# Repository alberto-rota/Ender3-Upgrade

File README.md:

# Ender3-Upgrade
A collection of upgrades and mods I installed on my Creality Ender 3.

This repository includes:
- A CAD model of the 3D printer, that includes the modifications made to the original design
- Downloadable `stl` files for the 3D printed parts
- The Marlin 2.0 firmware installed
- The PCB design for the custom electronic boards
  
***

<p align="center"> 
<a href="https://minhaskamal.github.io/DownGit/#/home?url=https://github.com/alberto-rota/Ender3-Upgrade/Printables">
<picture>
  <source media="(prefers-color-scheme: dark)" srcset="readme/download_stls_light.png">
   
</picture>
</a> </p>
All parts have been printed in standard 1.75 PLA filament, with a 4mm nozzle. They can be printer on any 3D printer, from hobbyist to professional. Print settings change depending on the part and the printer, but as long as a good bed adhesion is achieved, all parts will come out fine. The only part that requires a bit of support material in some place is the "Back case".

***
## Overview
The full Ender3 printer complete with all the upgrades is depicted below:

***
### Print Server
A Raspberry Pi 3A+ is used to host an OctoPrint server to remotely control and monitor the 3D printer. The Pi is powered from its separate power supply, connected to the printer via a USB cable, connected to the local network via WiFi (this was a limitation due to the available 3A+ model, a different model will be connected via Ethernet) and to an external USB webcam via a USB cable. A OTG USB hub (not in the picture) is necessary if using a 3A+

**NOTE:** This project was carried out during the COVID-19 pandemic, with the limited availability of electronics component (Pis cost more than 200€).

In order to control "high-power" components from Octoprint (USB lights, custom Noctua Fans), a custom PCB mounting a set of MOSFET switches was custom designed and integrated in the printer. The PCB mounts 2 Buck converters to step down the 24V of the Power supply to 5V (for the USB lights) and 12V (for the Noctua fans) and is connected to the Raspberry via the GPIO pins.

The render and the schematics of the PCS are shown below:

The Pi, PCB, hub and cables are all positioned into a custom 3D printed case, that is mounted in the V-slots of the aluminum extruded profiles.

***
### USB light bar

A USB LED strip is mounted on the top horizontal frame of the printer, to provide a light source for the print bed. Two supports were necessary in order to hold the magnets that came with the LED bar and that hold it in place. The supports and custom clips that hold the cable in place are custom and designed for the V-slots.
The lights are controlled via Octoprint through the GPIO plugin.

***
### Drawers
A set of 2 easy-access drawers have been positioned between the screen and the Y-Axis frame. The drawer container is, again, designed to fit in the V-slots of the aluminum extrusion.

Moreover, a set of 4 drawers has been placed behind the LCD screen of the printer. These drawers hold items which are more rarely accessed: nozzles, screws, springs, *etc.* The drwer container is held in place by the same screws that hold the LCD screen.

***
### Cable chain
A better cable management job was ensured with a set of cable covers that form a chain holding the cables tidy. One of this chain holds the cables that connect to the heated bed, the other holds the cables that connect to the extruder. The chain is mounted on the back of the printer, on the aluminum extrusion.

***
### Webcam Mount
A 3D printed mounting piece for a webcam. The shape and hole position are specific for the USB webcam I had at hand. The mount is designed to slide into the V-slots of the aluminum extruded profiles, with enough play to easily adjust its position along the extrusion.

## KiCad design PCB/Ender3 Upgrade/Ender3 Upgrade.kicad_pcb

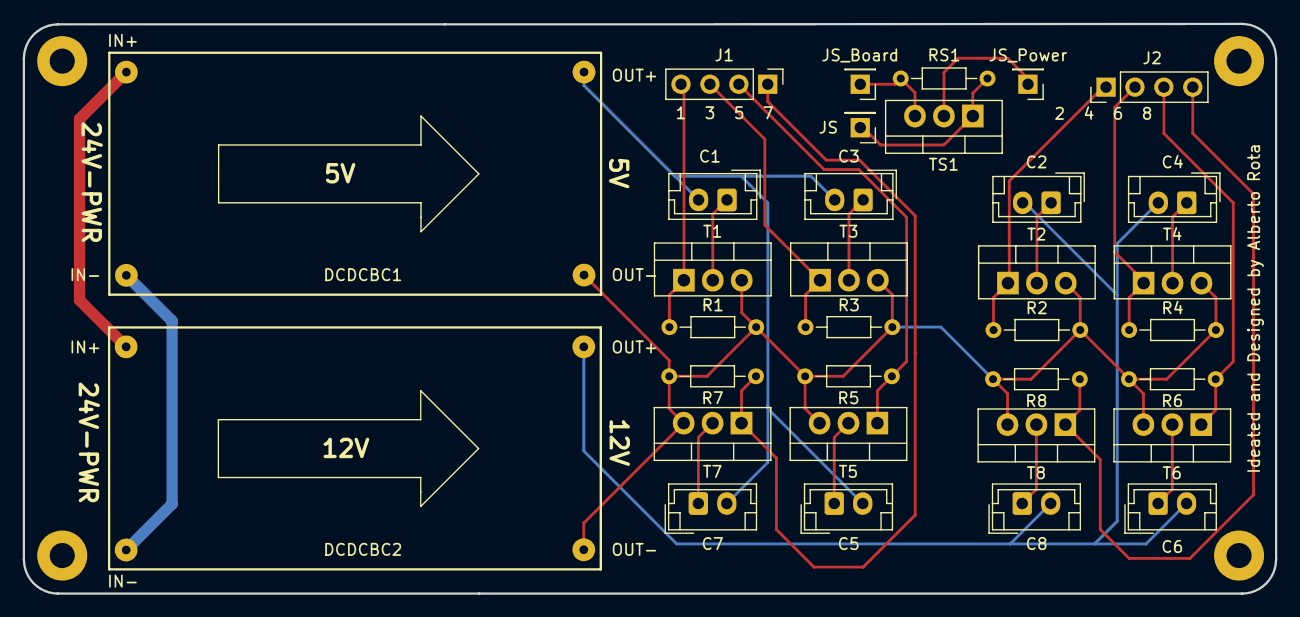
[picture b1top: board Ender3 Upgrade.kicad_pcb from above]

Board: 2 copper layers, 110.0 x 50.0 mm, 33 parts (0 on the bottom side), 24 nets.

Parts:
C1, C2, C3, C4, C5, C6, C7, C8: Conn_01x02; JST_EH_B2B-EH-A_1x02_P2.50mm_Vertical
DCDCBC1: DCDC 24-5; BuckConverter
DCDCBC2: DCDC 24-12; BuckConverter
J1, J2: Conn_01x04_Male; PinHeader_1x04_P2.54mm_Vertical
JS: Conn_01x01_Male; PinHeader_1x01_P2.54mm_Vertical
JS_Board: Conn_01x01_Male; PinHeader_1x01_P2.54mm_Vertical
JS_Power: Conn_01x01_Male; PinHeader_1x01_P2.54mm_Vertical
R1, R2, R3, R4, R5, R6, R7, R8: R1; R_Axial_DIN0204_L3.6mm_D1.6mm_P7.62mm_Horizontal
RS1: R1; R_Axial_DIN0204_L3.6mm_D1.6mm_P7.62mm_Horizontal
T1, T2, T3, T4, T5, T6, T7, T8: IRLZ34N; TO-220-3_Vertical
TS1: IRLZ34N; TO-220-3_Vertical

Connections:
5V: C1.2, C3.2, C5.2, C7.2, DCDCBC1.4
12V: C2.2, C4.2, C6.2, C8.2, DCDCBC2.4
+24V: DCDCBC1.2, DCDCBC2.2
GND: DCDCBC1.3, DCDCBC2.3, R1.2, R2.2, R3.2, R4.2, R5.2, R6.2, R7.2, R8.2, T1.3, T2.3, T3.3, T4.3, T5.3, T6.3, T7.3, T8.3
GNDPWR: DCDCBC1.1, DCDCBC2.1
unnamed: C1.1, T1.2
unnamed: C2.1, T2.2
unnamed: C3.1, T3.2
unnamed: C4.1, T4.2
unnamed: C5.1, T5.2
unnamed: C6.1, T6.2
unnamed: C7.1, T7.2
unnamed: C8.1, T8.2
unnamed: J1.1, R7.1, T7.1
unnamed: J1.2, R5.1, T5.1
unnamed: J1.3, R3.1, T3.1
unnamed: J1.4, R1.1, T1.1
unnamed: J2.1, R2.1, T2.1
unnamed: J2.2, R4.1, T4.1
unnamed: J2.3, R6.1, T6.1
unnamed: J2.4, R8.1, T8.1
unnamed: JS_Board.1, RS1.2, TS1.3
unnamed: JS.1, RS1.1, TS1.1
unnamed: JS_Power.1, TS1.2

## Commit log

2023-01-05 Firmware
2023-01-05 Initial update
2023-01-06 LED Wire Clip
2023-01-07 Fixes Conflicting Relationships
2023-01-09 Camera mount
2023-03-03 PCB Designed
2023-03-15 Drawers added
2023-03-15 Polished 3D models + Cool images
2023-03-28 Fixed
2023-03-28 test commit with bash alias
2023-03-28 test commit with bash alias - 2
2023-03-28 README made prettier
